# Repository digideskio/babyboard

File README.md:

# babyboard
A required example Schematic and PCB for Senior Capstone

Ensure Eagle is configured to search "lbr" of this project for libraries.

Ensure you also have the following libraries installed:

https://github.com/adafruit/Adafruit-Eagle-Library

https://github.com/sparkfun/SparkFun-Eagle-Libraries

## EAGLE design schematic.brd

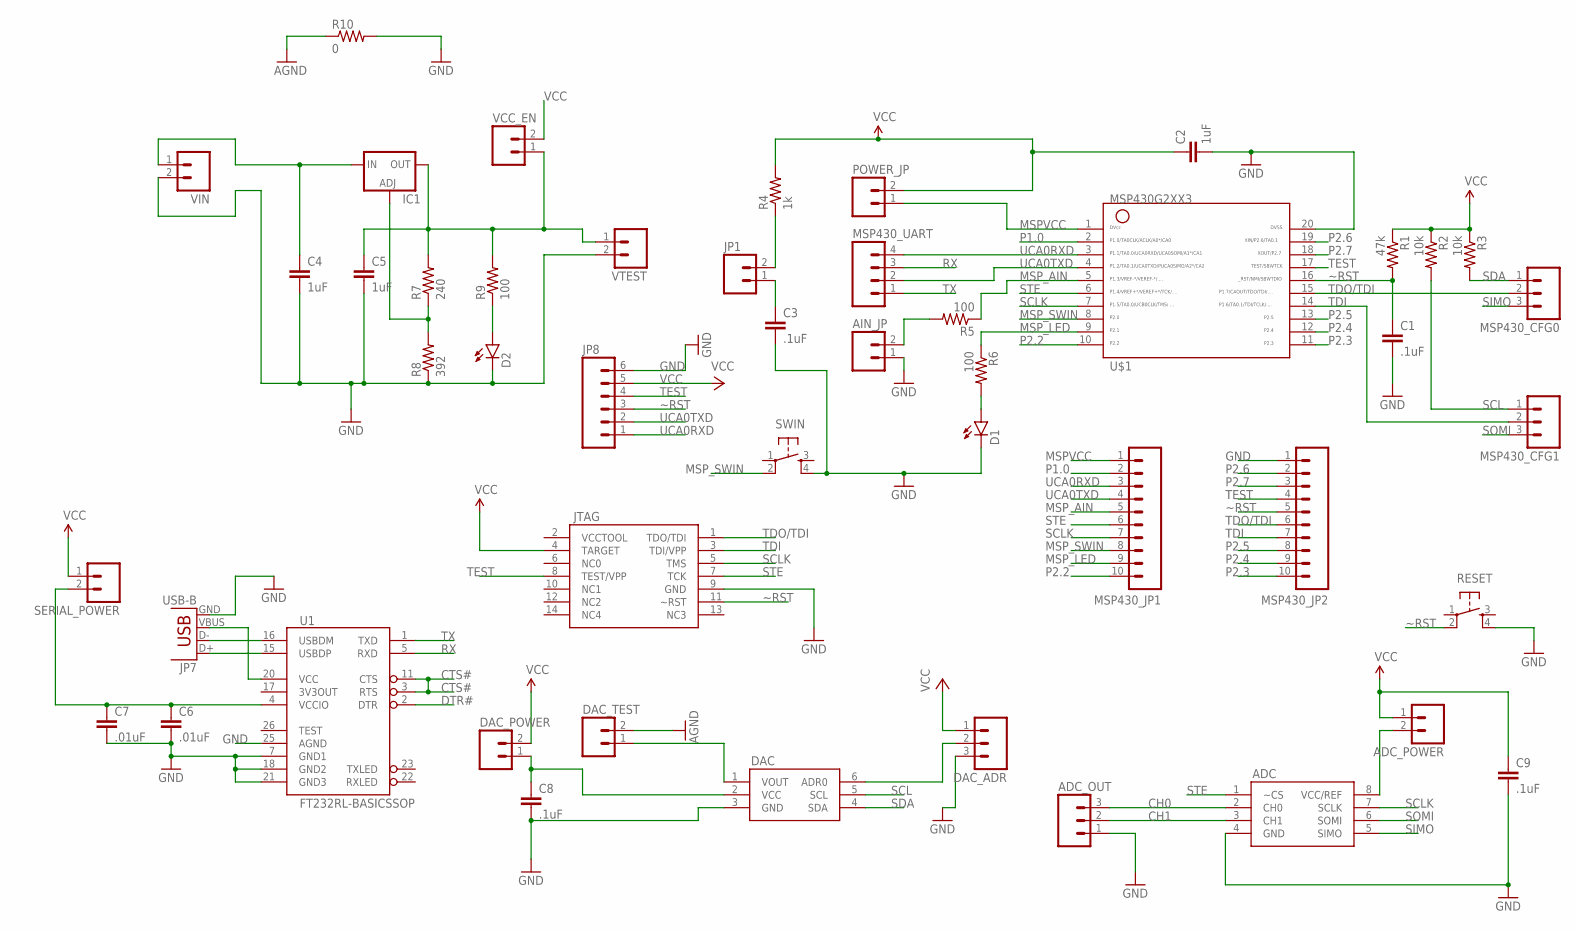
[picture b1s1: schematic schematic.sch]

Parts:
ADC: TLC0832CPE4; DIP08
ADC_OUT: M03LOCK; 1X03_LOCK
ADC_POWER: M02LOCK; 1X02_LOCK
AIN_JP: M02LOCK; 1X02_LOCK
C1: .1uF; CAP-PTH-SMALL-KIT
C2: 1uF; CAP-PTH-SMALL-KIT
C3, C8, C9: .1uF; CAP-PTH-SMALLEZ
C4, C5: 1uF; CAP-PTH-SMALLEZ
C6, C7: .01uF; CAP-PTH-SMALLEZ
D1, D2: LED5MM
DAC: DAC121C081CIMK; SOT23-6
DAC_ADR: M03LOCK; 1X03_LOCK
DAC_POWER: M02LOCK; 1X02_LOCK
DAC_TEST: M02LOCK; 1X02_LOCK
IC1: LM317TS; 317TS
JP1: M02LOCK; 1X02_LOCK
JP7: USB-B; USB-B-PTH
JP8: M06LOCK; 1X06_LOCK
JTAG: JTAG; 2X7
MSP430_CFG0, MSP430_CFG1: M03LOCK_NO_SILK; 1X03_LOCK_NO_SILK
MSP430_JP1, MSP430_JP2: M10LOCK; 1X10_LOCK
MSP430_UART: M04LOCK_LONGPADS; 1X04_LOCK_LONGPADS
POWER_JP: M02LOCK; 1X02_LOCK
R1: 47k; AXIAL-0.3EZ
R2, R3: 10k; AXIAL-0.3EZ
R4: 1k; AXIAL-0.3EZ
R5, R6, R9: 100; AXIAL-0.3EZ
R7: 240; AXIAL-0.3EZ
R8: 392; AXIAL-0.3EZ
R10: 0; AXIAL-0.3EZ
RESET: TAC_SWITCHPTH; TACTILE-PTH
SERIAL_POWER: M02LOCK; 1X02_LOCK
SWIN: TAC_SWITCHPTH; TACTILE-PTH
U1: FT232RL-BASICSSOP; SSOP28DB
U$1: G2XX3---N20; N20
VCC_EN: M02LOCK; 1X02_LOCK
VIN: M02LOCK; 1X02_LOCK
VTEST: M02LOCK; 1X02_LOCK

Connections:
CH0: ADC.2 (CH0), ADC_OUT.3
CH1: ADC.3 (CH1), ADC_OUT.2
CTS#: U1.3 (RTS), U1.11 (CTS)
DTR#: U1.2 (DTR)
GND: ADC.4 (GND), ADC_OUT.1, AIN_JP.1, C1.2, C2.2, C3.2, C4.2, C5.2, C6.2, C7.2, C8.2, C9.2, D1.K (C), D2.K (C), DAC.3 (GND), DAC_ADR.3, DAC_TEST.2, JP7.GND, JP8.6, JTAG.9 (GND), MSP430_JP2.1, R8.P$1 (1), R10.P$1 (1), R10.P$2 (2), RESET.4, SWIN.4, U1.7 (GND1), U1.18 (GND2), U1.21 (GND3), U1.25 (AGND), U$1.20, VIN.2, VTEST.2
MSPVCC: MSP430_JP1.1, POWER_JP.1, U$1.1
MSP_AIN: MSP430_JP1.5, R5.P$1 (1), U$1.5
MSP_LED: MSP430_JP1.9, R6.P$1 (1), U$1.9
MSP_SWIN: MSP430_JP1.8, SWIN.2, U$1.8
unnamed: AIN_JP.2, R5.P$2 (2)
unnamed: D1.A, R6.P$2 (2)
unnamed: JP1.2, R4.P$1 (1)
unnamed: C3.1, JP1.1
unnamed: C6.1, C7.1, SERIAL_POWER.2, U1.4 (VCCIO)
unnamed: D2.A, R9.P$1 (1)
unnamed: JP7.D+, U1.15 (USBDP)
unnamed: IC1.1 (ADJ), R7.P$1 (1), R8.P$2 (2)
unnamed: C5.1, IC1.2 (OUT), R7.P$2 (2), R9.P$2 (2), VCC_EN.1, VTEST.1
unnamed: JP7.D-, U1.16 (USBDM)
unnamed: C4.1, IC1.3 (IN), VIN.1
unnamed: JP7.VBUS, U1.20 (VCC)
unnamed: DAC.1 (VOUT), DAC_TEST.1
unnamed: C8.1, DAC.2 (VCC), DAC_POWER.1
unnamed: ADC.8 (VCC/REF), ADC_POWER.2
unnamed: DAC.6 (ADR0), DAC_ADR.2
P1.0: MSP430_JP1.2, U$1.2
P2.2: MSP430_JP1.10, U$1.10
P2.3: MSP430_JP2.10, U$1.11
P2.4: MSP430_JP2.9, U$1.12
P2.5: MSP430_JP2.8, U$1.13
P2.6: MSP430_JP2.2, U$1.19
P2.7: MSP430_JP2.3, U$1.18
RX: MSP430_UART.3, U1.5 (RXD)
SCL: DAC.5 (SCL), MSP430_CFG1.1, R2.P$2 (2)
SCLK: ADC.7 (SCLK), JTAG.5 (TMS), MSP430_JP1.7, U$1.7
SDA: DAC.4 (SDA), MSP430_CFG0.1, R3.P$2 (2)
SIMO: ADC.5 (SIMO), MSP430_CFG0.3
SOMI: ADC.6 (SOMI), MSP430_CFG1.3
STE: ADC.1 (~CS), JTAG.7 (TCK), MSP430_JP1.6, U$1.6
TDI: JTAG.3 (TDI/VPP), MSP430_CFG1.2, MSP430_JP2.7, U$1.14
TDO/TDI: JTAG.1 (TDO/TDI), MSP430_CFG0.2, MSP430_JP2.6, U$1.15
TEST: JP8.4, JTAG.8 (TEST/VPP), MSP430_JP2.4, U$1.17
TX: MSP430_UART.1, U1.1 (TXD)
UCA0RXD: JP8.1, MSP430_JP1.3, MSP430_UART.4, U$1.3
UCA0TXD: JP8.2, MSP430_JP1.4, MSP430_UART.2, U$1.4
VCC: ADC_POWER.1, C2.1, C9.1, DAC_ADR.1, DAC_POWER.2, JP8.5, JTAG.4 (TARGET), POWER_JP.2, R1.P$1 (1), R2.P$1 (1), R3.P$1 (1), R4.P$2 (2), SERIAL_POWER.1, VCC_EN.2
~RST: C1.1, JP8.3, JTAG.11 (~RST), MSP430_JP2.5, R1.P$2 (2), RESET.2, U$1.16

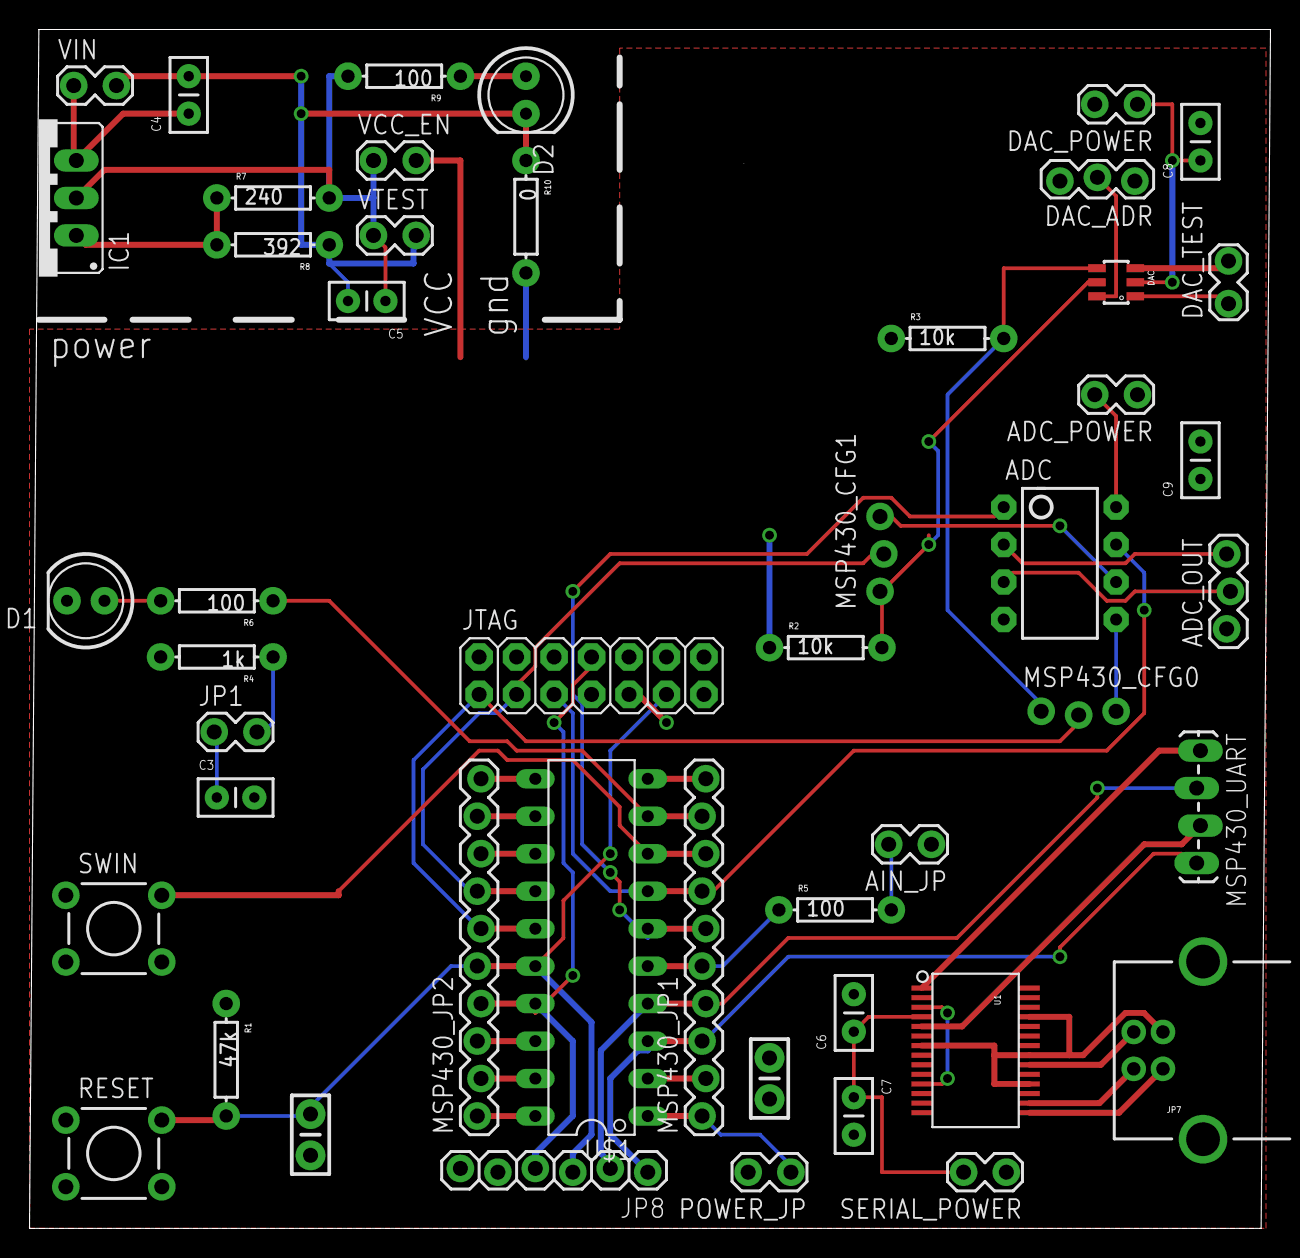
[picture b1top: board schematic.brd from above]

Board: 2 copper layers, 84.1 x 81.3 mm, 48 parts (0 on the bottom side), 46 nets.

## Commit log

2015-09-15 first commit of babyboard
2015-09-16 inital routing complete
2015-09-22 finishing up layout

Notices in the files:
parts and their libraries:
SparkFun-Connectors: Licensing: Creative Commons ShareAlike 4.0 International - https://creativecommons.org/licenses/by-sa/4.0
